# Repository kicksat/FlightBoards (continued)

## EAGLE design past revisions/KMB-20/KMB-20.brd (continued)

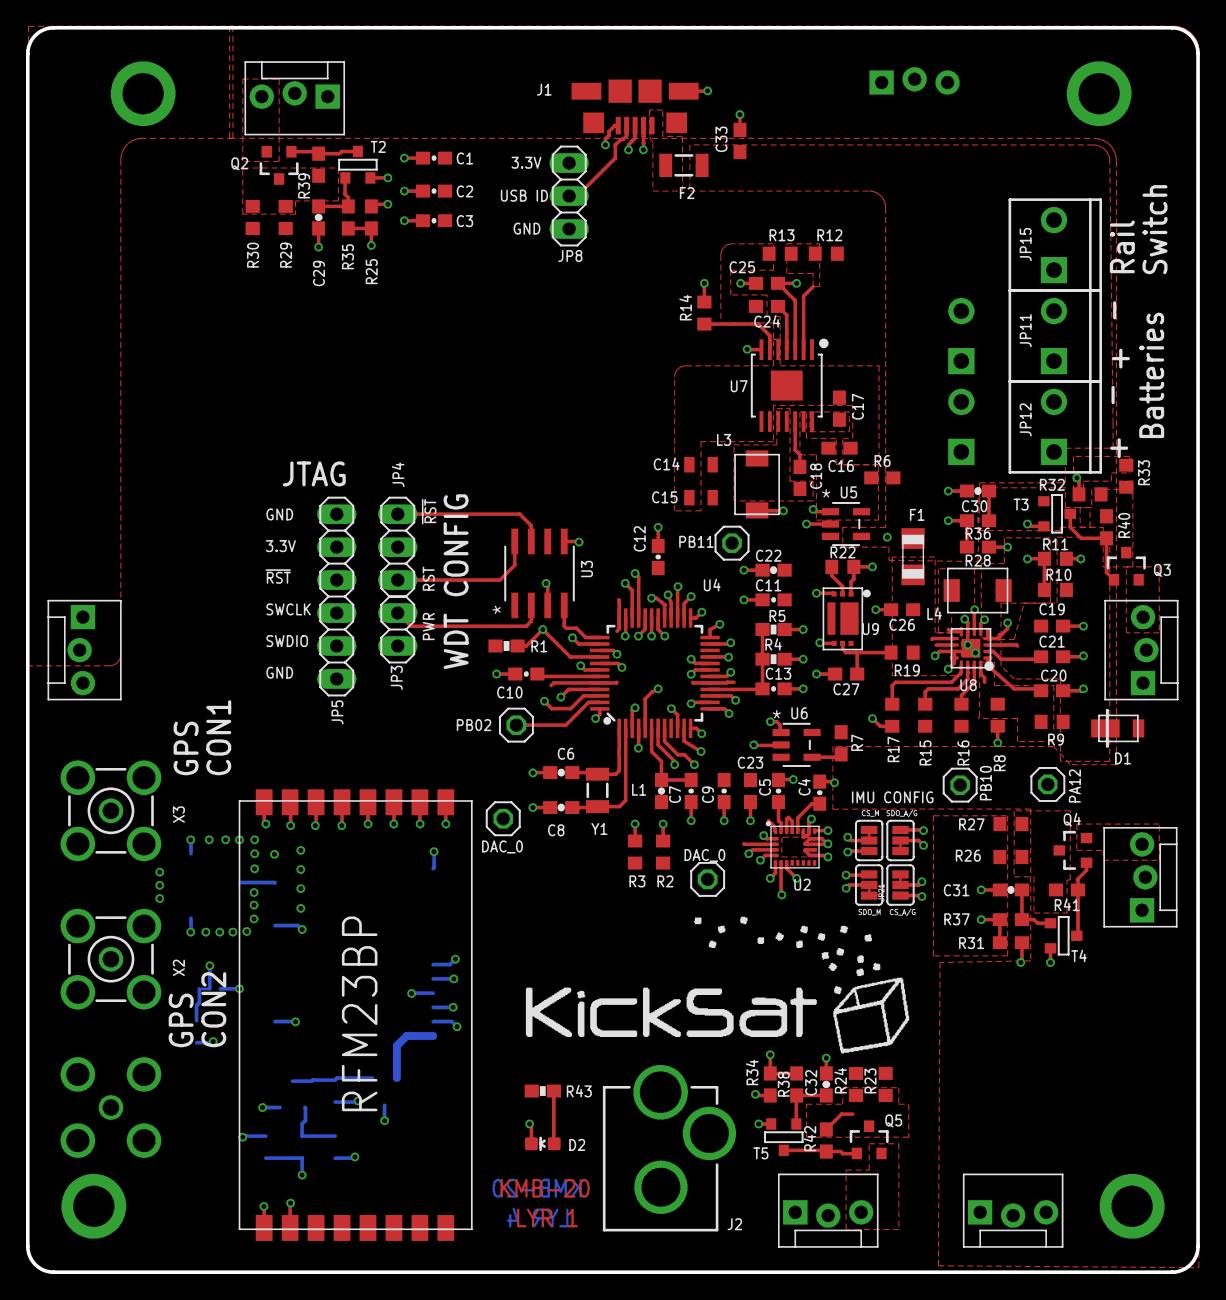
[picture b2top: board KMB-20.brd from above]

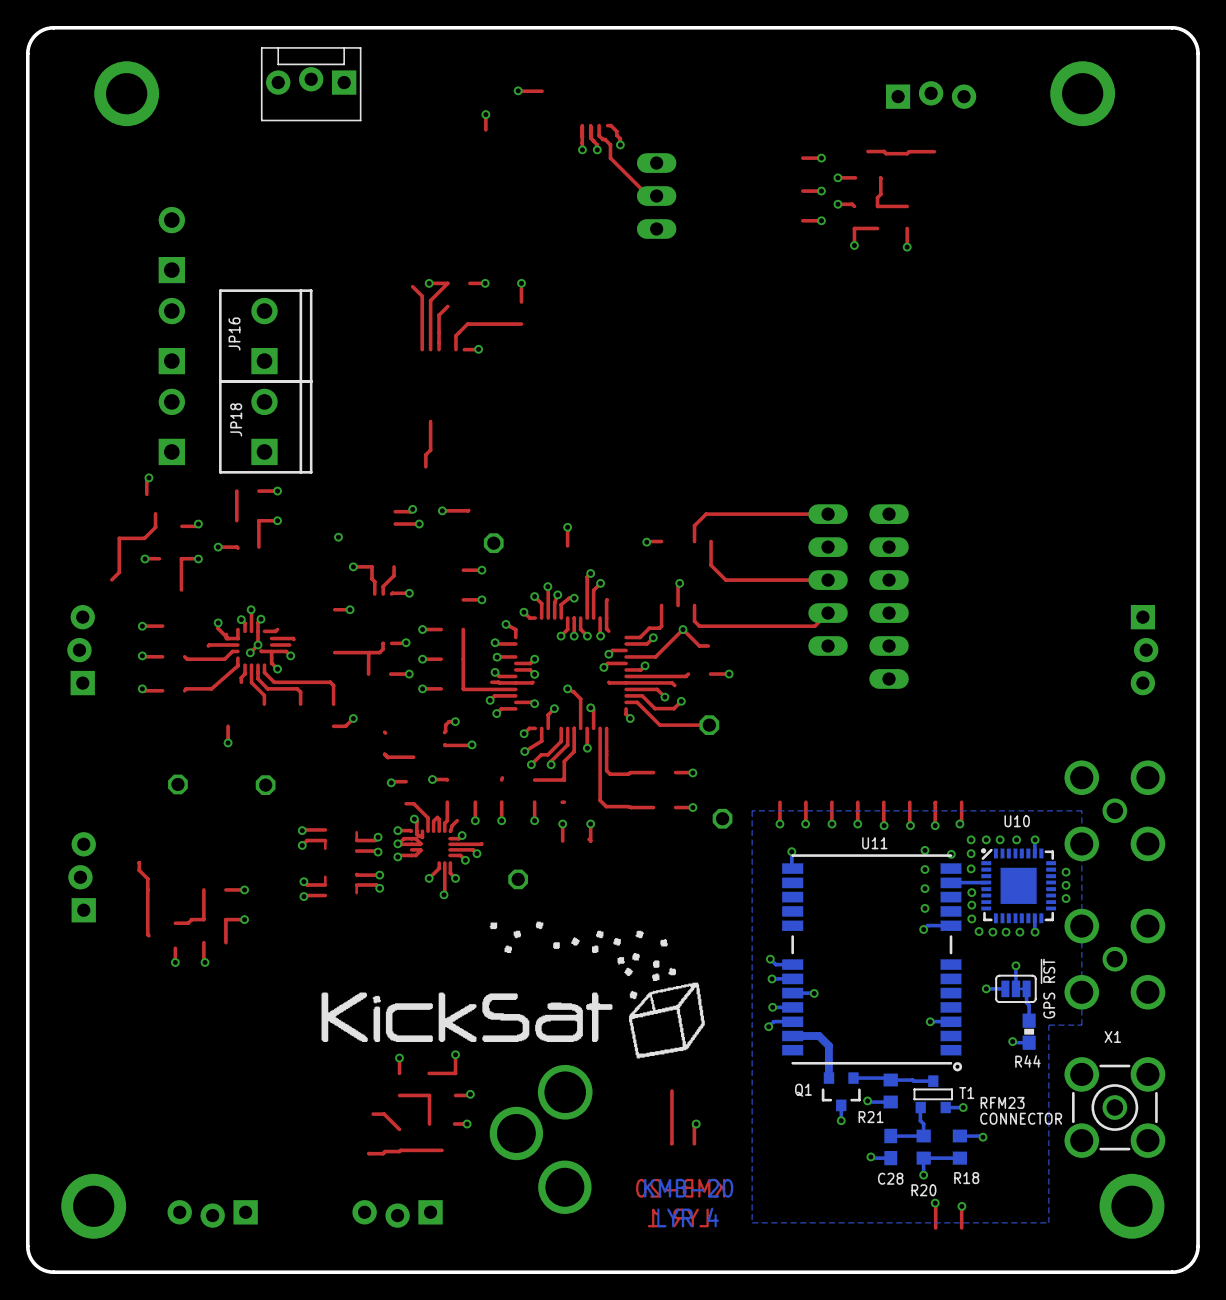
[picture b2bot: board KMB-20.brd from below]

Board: 4 copper layers, 90.2 x 95.9 mm, 144 parts (15 on the bottom side), 100 nets.

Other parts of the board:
L5: KICKSAT_LOGO

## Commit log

2018-04-11 Initial commit of new KickSat-2 board
2018-06-01 Latest kicksat2 mainboard update (KMB-21). New from KMB-20: MRAM, power relays, microSD card, 2 spots for [XLab Tester Boards](https://github.com/maholli/XTB)
2018-06-05 Adding datasheets
2018-06-07 adding KMB-21 BOM
2018-06-26 ensuring latest
2018-06-26 adding pdf of schematic
2018-06-26 first commit of design discussion
2018-06-26 adding SAMD21 related datasheets
2018-06-27 updated justification with hardware figure
2018-06-27 added burnwire diagram
2018-06-27 added schematic
2018-07-10 Add files via upload
    Conops Diagram 07/10/18
    To be discussed at the 3pm meeting
2018-07-10 Motherboard IMU
2018-07-10 Add files via upload
    Editable version of the conops diagram as a powerpoint
2018-07-20 Set theme jekyll-theme-midnight
2018-07-21 added MRAM datasheet
2018-07-25 added KMB-22 design
2018-07-25 fixed schematic output error
2018-07-25 updated schematic export errors
2018-07-25 KMB-22 schematic update
2018-07-25 changed solar panel connector on KMB-22
2018-07-28 KMB-20 schematic
2018-08-02 added reset instructions for KMB21
2018-08-08 added data sheet for SAMD21 chip rev C
2018-08-08 moved file to folder
2018-08-13 adding WDT disable how-to
2018-08-13 fixing folder name
2018-08-15 adding missing schematic pages
2018-08-22 added KMB-23
2018-08-22 updated mainboard to KMB-23
2018-09-19 added KMB-24
